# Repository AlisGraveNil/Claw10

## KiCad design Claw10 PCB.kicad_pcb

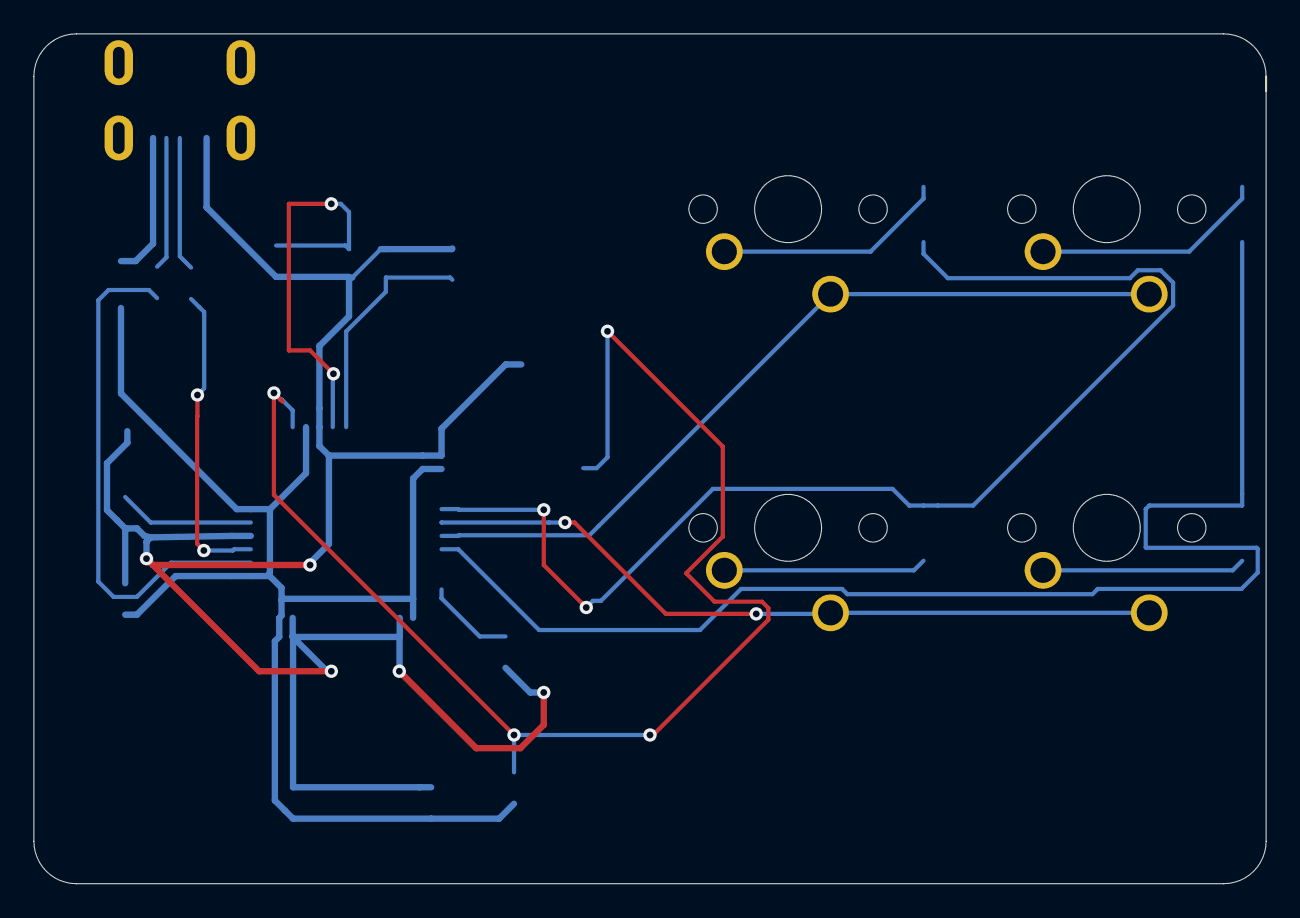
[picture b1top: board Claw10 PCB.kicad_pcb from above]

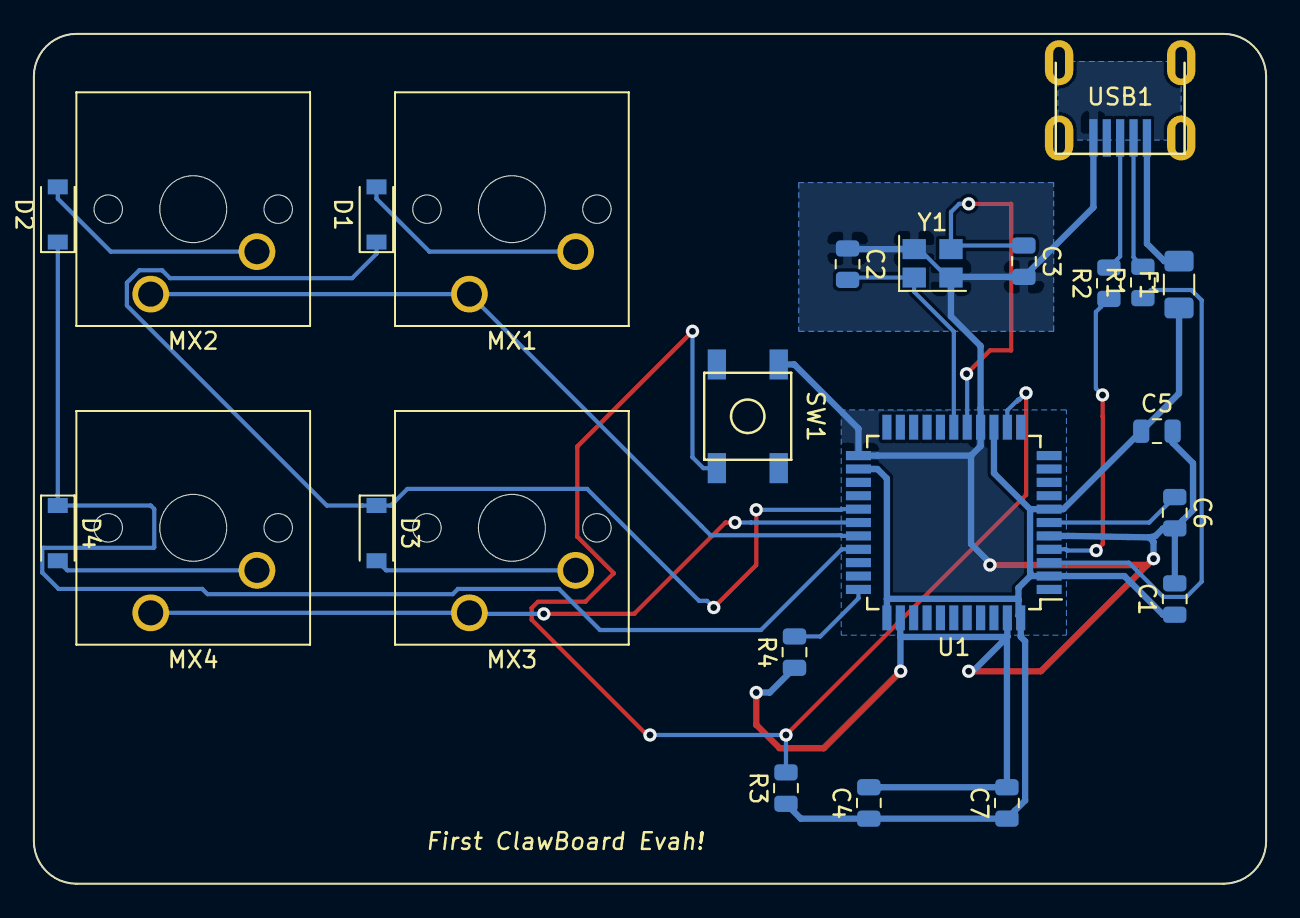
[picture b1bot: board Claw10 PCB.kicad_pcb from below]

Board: 2 copper layers, 73.7 x 50.8 mm, 24 parts (24 on the bottom side), 20 nets.

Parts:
C1, C4: 0.1uF; C_0805_2012Metric
C2, C3: 22pF; C_0805_2012Metric
C5: 0.1uf; C_0805_2012Metric
C6: 1uF; C_0805_2012Metric
C7: 10uF; C_0805_2012Metric
D1, D2, D3, D4: SOD-123; D_SOD-123
F1: 500mA; Fuse_1206_3216Metric
MX1, MX2, MX3, MX4: MX-NoLED; SW_Cherry_MX_1.00u_PCB
R1, R2: 22; R_0805_2012Metric
R3, R4: 10k; R_0805_2012Metric
SW1: SW_Push; SKQG-1155865
U1: ATmega32U4-AU; TQFP-44_10x10mm_P0.8mm
USB1: Molex-0548190589
Y1: 16MHz; Crystal_SMD_3225-4Pin_3.2x2.5mm

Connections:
+5V: C1.1, C4.1, C5.1, C7.1, F1.1, R3.1, U1.2, U1.7, U1.14, U1.24, U1.34, U1.44
COL0: MX1.1, MX2.1, U1.29
COL1: MX3.1, MX4.1, U1.28
D+: R2.2, USB1.3
D-: R1.2, USB1.4
GND: C1.2, C2.1, C3.2, C4.2, C5.2, C6.2, C7.2, R4.1, SW1.1, U1.5, U1.15, U1.23, U1.35, U1.43, USB1.1, Y1.2, Y1.4
unnamed: C2.2, U1.17, Y1.1
unnamed: C3.1, U1.16, Y1.3
unnamed: C6.1, U1.6
unnamed: D1.2, MX1.2
unnamed: D2.2, MX2.2
unnamed: D3.2, MX3.2
unnamed: D4.2, MX4.2
unnamed: R1.1, U1.3
unnamed: R2.1, U1.4
unnamed: R3.2, SW1.2, U1.13
unnamed: R4.2, U1.33
ROW0: D1.1, D3.1, U1.27
ROW1: D2.1, D4.1, U1.30
VCC: F1.2, USB1.5

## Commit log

2020-04-01 Claw10
    A 10-key macropad - first board ever
2020-04-02 4/2/20
2020-04-02 4/2/20 v2
2020-04-03 4/3/20
2020-04-03 4/3/20 v2
2020-04-03 4/3/20 v3
2020-04-03 4/3/20 v4
